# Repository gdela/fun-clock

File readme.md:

Alarm Clock with Oversleep Prevention
=====================================

Features:

- automatic time synchronization with NTP server over WiFi
- old-style TIL311 hexadecimal display
- two alarm settings: for weekdays and for weekends
- alarm starts gently with some nature sounds for a couple of minutes
- alarm ends with very loud energetic music to make sure you hear it
- to turn alarm off you need to read three random numbers and enter them back
- this makes sure that you are fully awake and do not oversleep the alarm

There is no documentation for this project, as this is rather for my own purposes.
Feel free to reverse-engineer it.

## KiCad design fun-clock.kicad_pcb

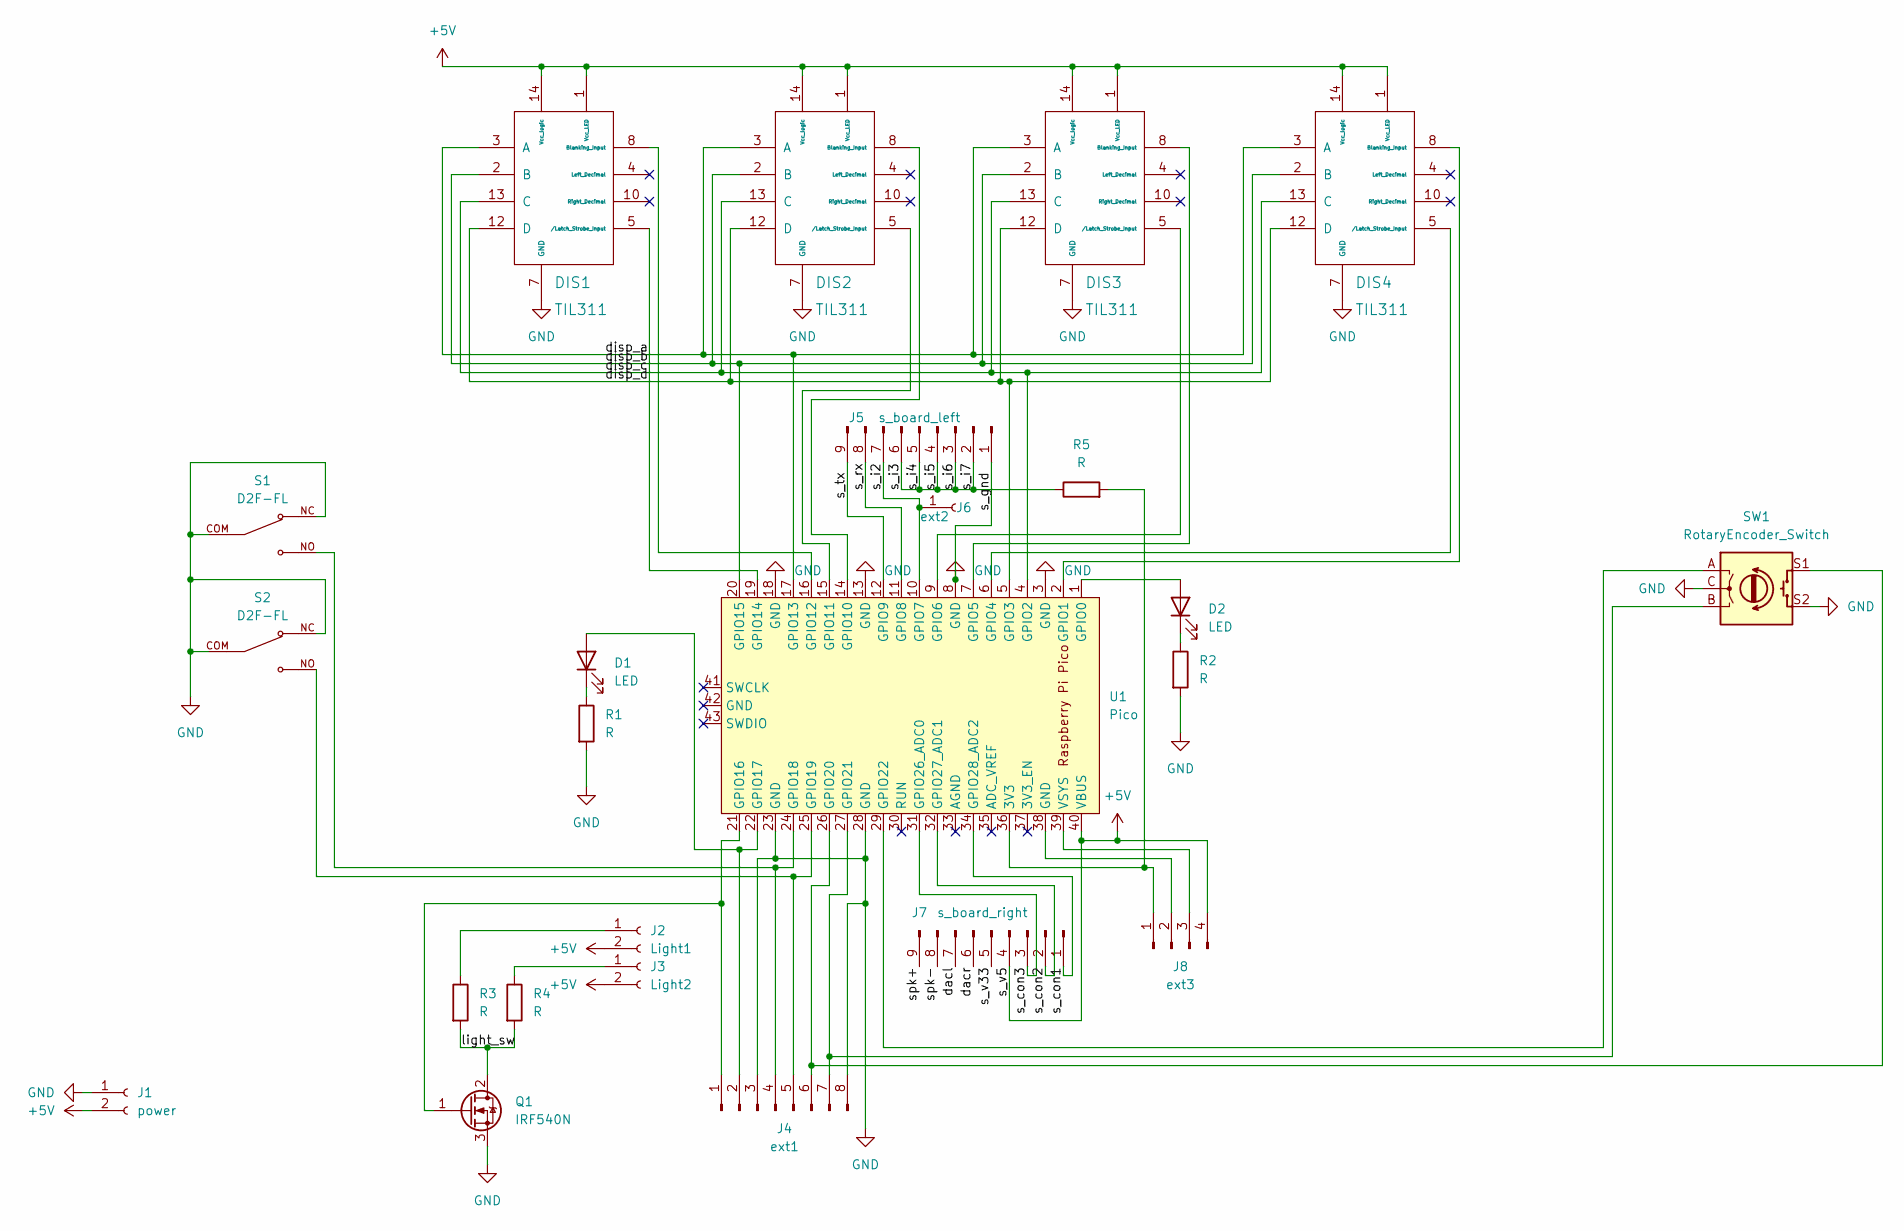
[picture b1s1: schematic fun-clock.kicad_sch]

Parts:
D1, D2: LED; LED_Rectangular_W5.0mm_H2.0mm
DIS1, DIS2, DIS3, DIS4: TIL311
J1: power; TerminalBlock_bornier-2_P5.08mm
J2: Light1; SolderWire-0.5sqmm_1x02_P4.8mm_D0.9mm_OD2.3mm
J3: Light2; SolderWire-0.5sqmm_1x02_P4.8mm_D0.9mm_OD2.3mm
J4: ext1; PinHeader_1x08_P2.54mm_Vertical
J5: s_board_left; PinHeader_1x09_P2.54mm_Vertical
J6: ext2; TestPoint_Pad_2.0x2.0mm
J7: s_board_right; PinHeader_1x09_P2.54mm_Vertical
J8: ext3; PinHeader_1x04_P2.54mm_Vertical
Q1: IRF540N; TO-220-3_Horizontal_TabDown
R1, R2, R5: R; R_Axial_DIN0207_L6.3mm_D2.5mm_P10.16mm_Horizontal
R3, R4: R; R_Axial_DIN0414_L11.9mm_D4.5mm_P15.24mm_Horizontal
S1, S2: D2F-FL; SW_D2F-FL; PARTREV N/A
SW1: RotaryEncoder_Switch; mojenkoder
U1: Pico; RPi_Pico_SMD_TH

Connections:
+5V: DIS1.1 (Vcc_LED), DIS1.14 (Vcc_logic), DIS2.1 (Vcc_LED), DIS2.14 (Vcc_logic), DIS3.1 (Vcc_LED), DIS3.14 (Vcc_logic), DIS4.1 (Vcc_LED), DIS4.14 (Vcc_logic), J1.2, J2.2, J3.2, J7.4, J8.4, U1.40 (VBUS)
/dacl: J7.7
/dacr: J7.6
/disp_a: DIS1.3 (A), DIS2.3 (A), DIS3.3 (A), DIS4.3 (A), U1.17 (GPIO13)
/disp_b: DIS1.2 (B), DIS2.2 (B), DIS3.2 (B), DIS4.2 (B), U1.20 (GPIO15)
/disp_c: DIS1.13 (C), DIS2.13 (C), DIS3.13 (C), DIS4.13 (C), U1.4 (GPIO2)
/disp_d: DIS1.12 (D), DIS2.12 (D), DIS3.12 (D), DIS4.12 (D), U1.5 (GPIO3)
/light_sw: Q1.2 (D), R3.2, R4.2
/s_con1: J7.1, U1.34 (GPIO28_ADC2)
/s_con2: J7.2, U1.32 (GPIO27_ADC1)
/s_con3: J7.3, U1.31 (GPIO26_ADC0)
/s_i2: J5.7, J6.1, U1.10 (GPIO7)
/s_i3: J5.2, J5.3, J5.4, J5.5, J5.6, R5.1
/s_rx: J5.8, U1.11 (GPIO8)
/s_tx: J5.9, U1.12 (GPIO9)
/s_v33: J7.5
/spk+: J7.9
/spk-: J7.8
GND: DIS1.7 (GND), DIS2.7 (GND), DIS3.7 (GND), DIS4.7 (GND), J1.1, J4.3, J4.8, J5.1, Q1.3 (S), R1.2, R2.2, S1.COM, S1.NC, S2.COM, S2.NC, SW1.C, SW1.S2, U1.3 (GND), U1.8 (GND), U1.13 (GND), U1.18 (GND), U1.23 (GND), U1.28 (GND)
unnamed: D1.1 (K), R1.1
unnamed: D1.2 (A), J4.2, U1.22 (GPIO17)
unnamed: D2.1 (K), R2.1
unnamed: D2.2 (A), U1.1 (GPIO0)
unnamed: DIS1.5 (/Latch_Strobe_Input), U1.19 (GPIO14)
unnamed: DIS1.8 (Blanking_Input), U1.16 (GPIO12)
unnamed: DIS2.5 (/Latch_Strobe_Input), U1.15 (GPIO11)
unnamed: DIS2.8 (Blanking_Input), U1.14 (GPIO10)
unnamed: DIS3.5 (/Latch_Strobe_Input), U1.9 (GPIO6)
unnamed: DIS3.8 (Blanking_Input), U1.7 (GPIO5)
unnamed: DIS4.5 (/Latch_Strobe_Input), U1.6 (GPIO4)
unnamed: DIS4.8 (Blanking_Input), U1.2 (GPIO1)
unnamed: J2.1, R3.1
unnamed: J3.1, R4.1
unnamed: J4.1, Q1.1 (G), U1.21 (GPIO16)
unnamed: J4.4, S1.NO, U1.24 (GPIO18)
unnamed: J4.5, S2.NO, U1.25 (GPIO19)
unnamed: J4.6, SW1.S1, U1.26 (GPIO20)
unnamed: J4.7, SW1.B, U1.27 (GPIO21)
unnamed: J8.1, R5.2, U1.36 (3V3)
unnamed: J8.2, U1.38 (GND)
unnamed: J8.3, U1.39 (VSYS)
unnamed: SW1.A, U1.29 (GPIO22)

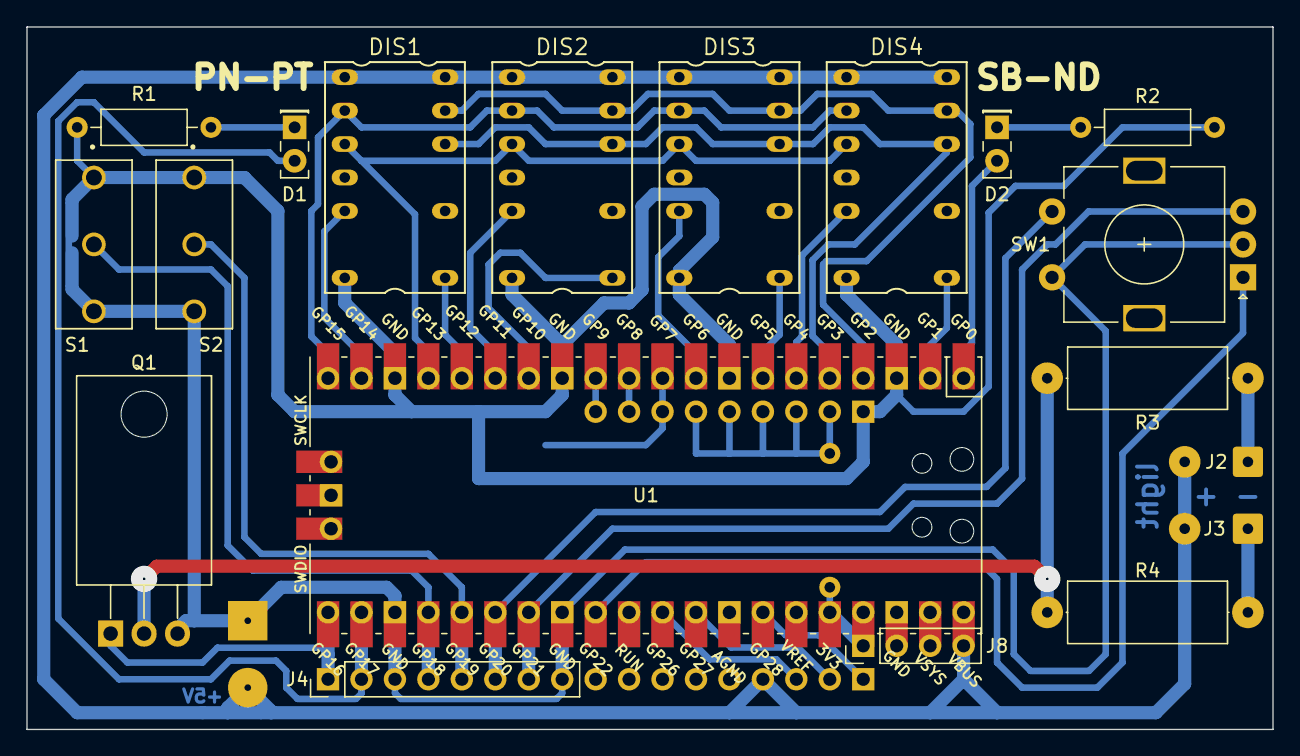
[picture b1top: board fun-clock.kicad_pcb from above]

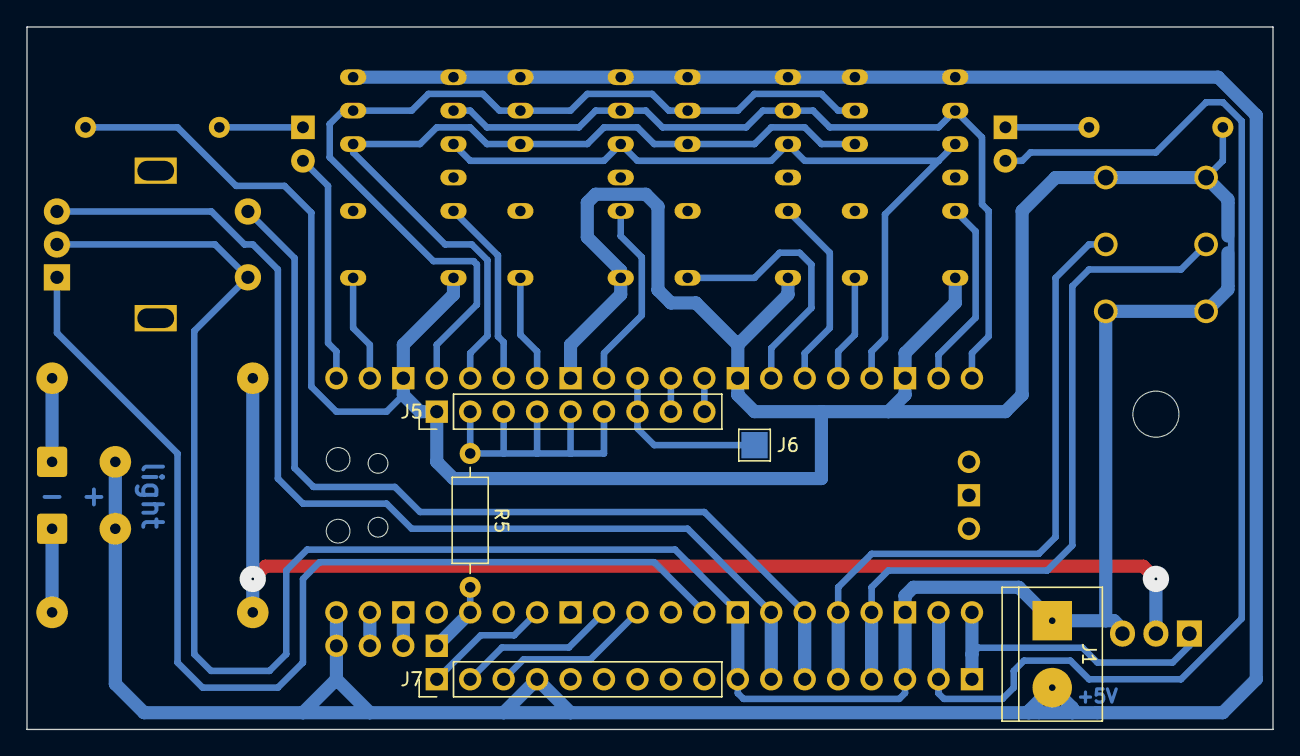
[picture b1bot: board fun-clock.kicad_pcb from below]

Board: 2 copper layers, 94.6 x 53.3 mm, 24 parts (5 on the bottom side), 37 nets.

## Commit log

2023-08-20 KiCad library for TIL311 display.
2023-08-20 PyCharm files update.
2023-08-20 Finished clock code.
2023-08-20 Sounds for the clock.
2023-08-20 Auto off if nobody responds to alarm.
2023-08-20 Description and picture of finished clock.
